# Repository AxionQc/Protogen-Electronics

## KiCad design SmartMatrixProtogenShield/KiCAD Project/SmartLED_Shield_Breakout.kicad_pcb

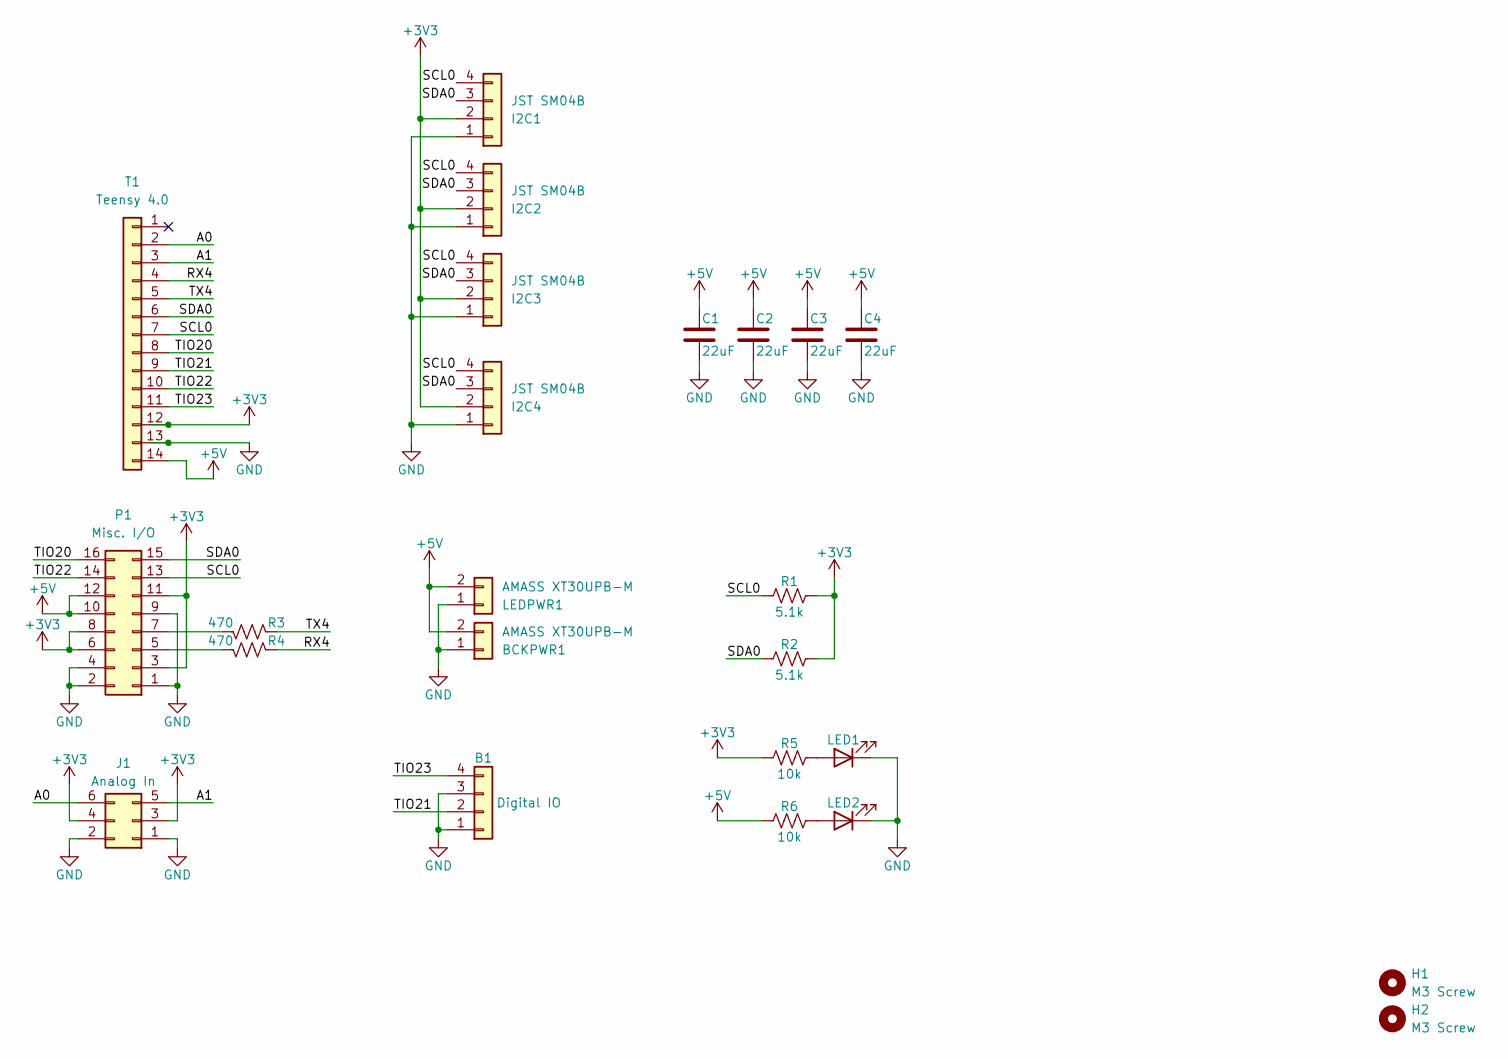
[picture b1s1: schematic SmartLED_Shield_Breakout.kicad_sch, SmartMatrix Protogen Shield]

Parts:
B1: Digital IO; PinHeader_1x04_P2.54mm_Vertical
BCKPWR1: AMASS XT30UPB-M; AMASS_XT30UPB-M_1x02_P5.0mm_Vertical
C1, C2, C3, C4: 22uF; C_0805_2012Metric_Pad1.18x1.45mm_HandSolder
H1, H2: M3 Screw; MountingHole_3.2mm_M3
I2C1, I2C2, I2C3, I2C4: JST SM04B; JST_SH_SM04B-SRSS-TB_1x04-1MP_P1.00mm_Horizontal
J1: Analog In; PinHeader_2x03_P2.54mm_Vertical
LED1, LED2: LED; LED_0805_2012Metric_Pad1.15x1.40mm_HandSolder
LEDPWR1: AMASS XT30UPB-M; AMASS_XT30UPB-M_1x02_P5.0mm_Vertical
P1: Misc. I/O; PinHeader_2x08_P2.54mm_Vertical
R1, R2: 5.1k; R_0805_2012Metric_Pad1.20x1.40mm_HandSolder
R3, R4: 470; R_0805_2012Metric_Pad1.20x1.40mm_HandSolder
R5, R6: 10k; R_0805_2012Metric_Pad1.20x1.40mm_HandSolder
T1: Teensy 4.0; PinHeader_1x14_P2.54mm_Vertical

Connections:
+3V3: I2C1.2, I2C2.2, I2C3.2, I2C4.2, J1.3, J1.4, P1.3, P1.6, P1.8, P1.11, R1.2, R2.2, R5.1, T1.12
+5V: BCKPWR1.2, C1.1, C2.1, C3.1, C4.1, LEDPWR1.2, P1.10, P1.12, R6.1, T1.14
/A0: J1.6, T1.2
/A1: J1.5, T1.3
/RX4: R4.1, T1.4
/SCL0: I2C1.4, I2C2.4, I2C3.4, I2C4.4, P1.13, R1.1, T1.7
/SDA0: I2C1.3, I2C2.3, I2C3.3, I2C4.3, P1.15, R2.1, T1.6
/TIO20: P1.16, T1.8
/TIO21: B1.2, T1.9
/TIO22: P1.14, T1.10
/TIO23: B1.4, T1.11
/TX4: R3.1, T1.5
GND: B1.1, B1.3, BCKPWR1.1, C1.2, C2.2, C3.2, C4.2, I2C1.1, I2C2.1, I2C3.1, I2C4.1, J1.1, J1.2, LED1.1 (K), LED2.1 (K), LEDPWR1.1, P1.1, P1.2, P1.4, P1.9, T1.13
unnamed: LED1.2 (A), R5.2
unnamed: LED2.2 (A), R6.2
unnamed: P1.5, R4.2
unnamed: P1.7, R3.2

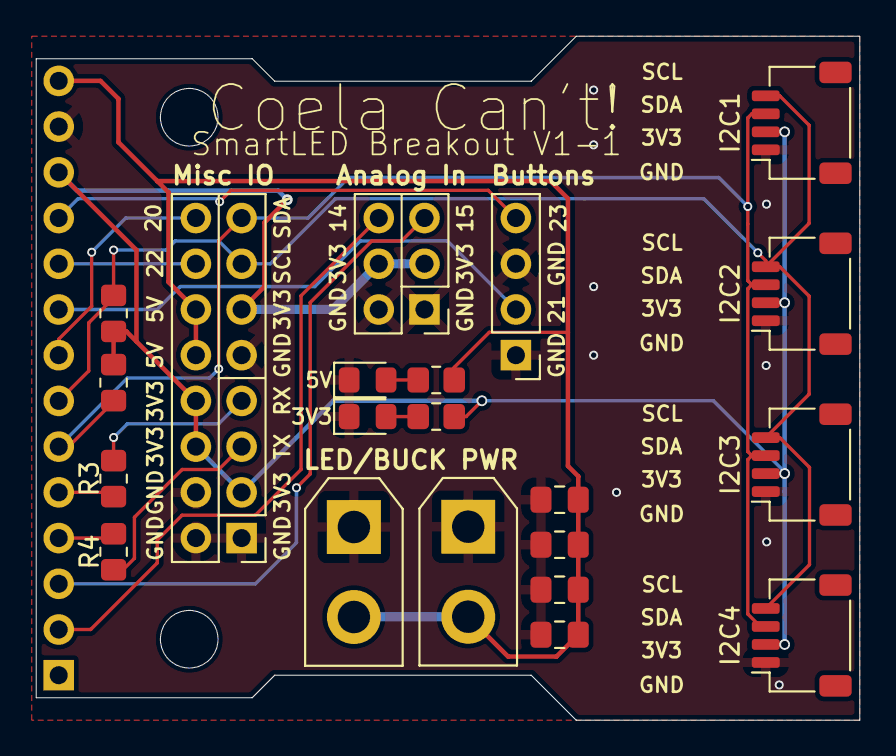
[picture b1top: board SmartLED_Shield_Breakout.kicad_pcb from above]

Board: 2 copper layers, 45.7 x 38.0 mm, 24 parts (0 on the bottom side), 17 nets.

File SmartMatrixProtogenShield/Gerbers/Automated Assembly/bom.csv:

Designator,Footprint,Quantity,Value,LCSC Part #
"BCKPWR1, LEDPWR1",AMASS_XT30UPB-M_1x02_P5.0mm_Vertical,2,AMASS XT30UPB-M,
"C1, C2, C3, C4",0805,4,22uF,
"I2C1, I2C2, I2C3, I2C4",JST_SH_SM04B-SRSS-TB_1x04-1MP_P1.00mm_Horizontal,4,JST SM04B,
"LED1, LED2",0805,2,LED,
"R1, R2",0805,2,5.1k,
"R3, R4",0805,2,470,
"R5, R6",0805,2,10k,

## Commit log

2026-01-19 Updated the Shield Breakout to use the Semma QT standard with JST SH headers.
    Updated Pinouts to refect current prototracer standards.
    Reduced I2c Resistor value to 5.1k to improve high speed performance
